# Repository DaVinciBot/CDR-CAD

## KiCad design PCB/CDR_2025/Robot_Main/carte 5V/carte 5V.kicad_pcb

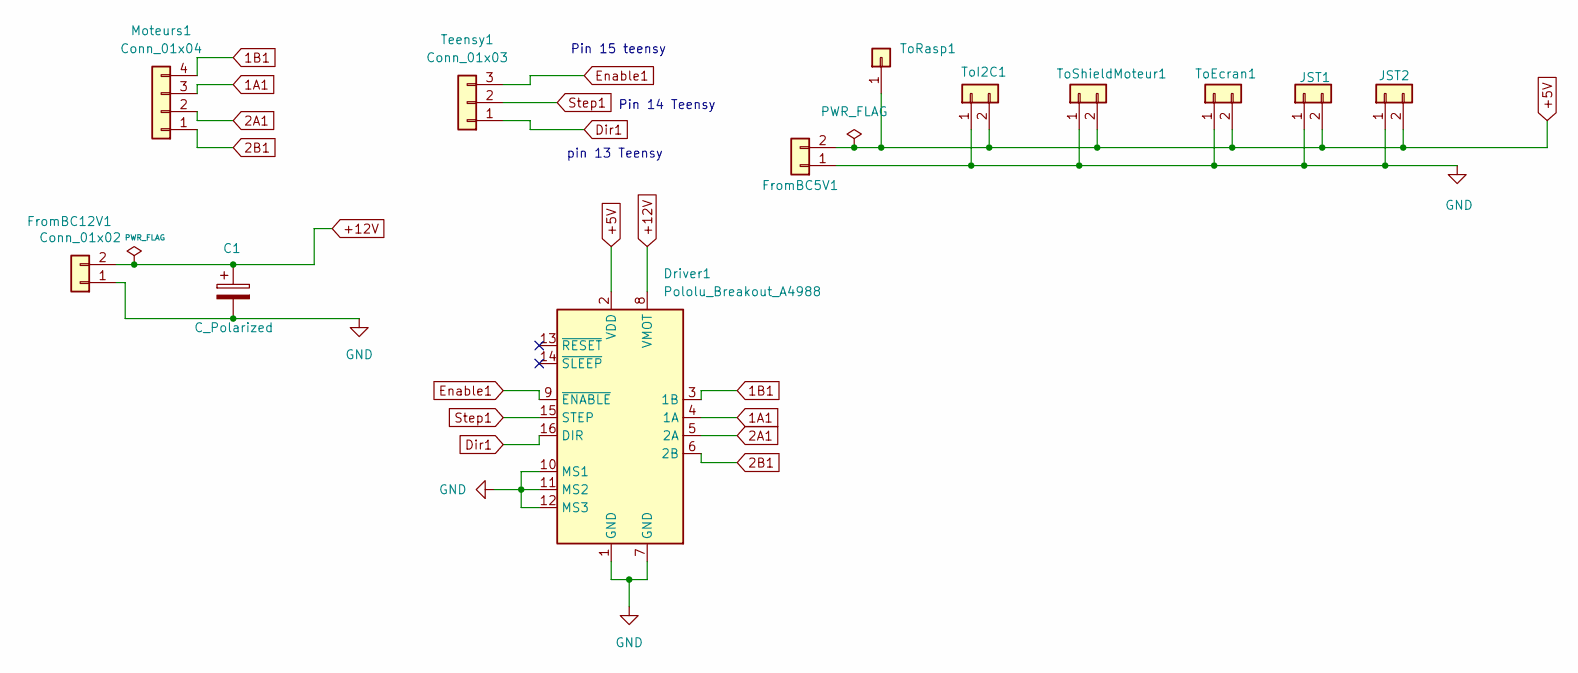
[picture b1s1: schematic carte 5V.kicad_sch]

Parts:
C1: C_Polarized; C_Radial_D12.5mm_H25.0mm_P5.00mm
Driver1: Pololu_Breakout_A4988; Pololu_Breakout-16_15.2x20.3mm
FromBC5V1, FromBC12V1: Conn_01x02; TerminalBlock_bornier-2_P5.08mm
JST1, JST2: Conn_01x02; JST_XH_B2B-XH-A_1x02_P2.50mm_Vertical
Moteurs1: Conn_01x04; JST_XH_B4B-XH-A_1x04_P2.50mm_Vertical
Teensy1: Conn_01x03; JST_XH_B3B-XH-A_1x03_P2.50mm_Vertical
ToEcran1: Conn_01x02; JST_XH_B2B-XH-A_1x02_P2.50mm_Vertical
ToI2C1: Conn_01x02; JST_XH_B2B-XH-A_1x02_P2.50mm_Vertical
ToRasp1: Conn_01x01; JST_XH_B1B-XH-AM_1x01_P2.50mm_Vertical
ToShieldMoteur1: Conn_01x02; JST_XH_B2B-XH-A_1x02_P2.50mm_Vertical

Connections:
1A1: Driver1.4 (1A), Moteurs1.3
1B1: Driver1.3 (1B), Moteurs1.4
2A1: Driver1.5 (2A), Moteurs1.2
2B1: Driver1.6 (2B), Moteurs1.1
+5V: Driver1.2 (VDD), FromBC5V1.2, JST1.2, JST2.2, ToEcran1.2, ToI2C1.2, ToRasp1.1, ToShieldMoteur1.2
+12V: C1.1, Driver1.8 (VMOT), FromBC12V1.2
Dir1: Driver1.16 (DIR), Teensy1.1
Enable1: Driver1.9 (~ENABLE), Teensy1.3
GND: C1.2, Driver1.1 (GND), Driver1.7 (GND), Driver1.10 (MS1), Driver1.11 (MS2), Driver1.12 (MS3), FromBC5V1.1, FromBC12V1.1, JST1.1, JST2.1, ToEcran1.1, ToI2C1.1, ToShieldMoteur1.1
Step1: Driver1.15 (STEP), Teensy1.2

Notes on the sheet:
Pin 15 teensy
Pin 14 Teensy
pin 13 Teensy

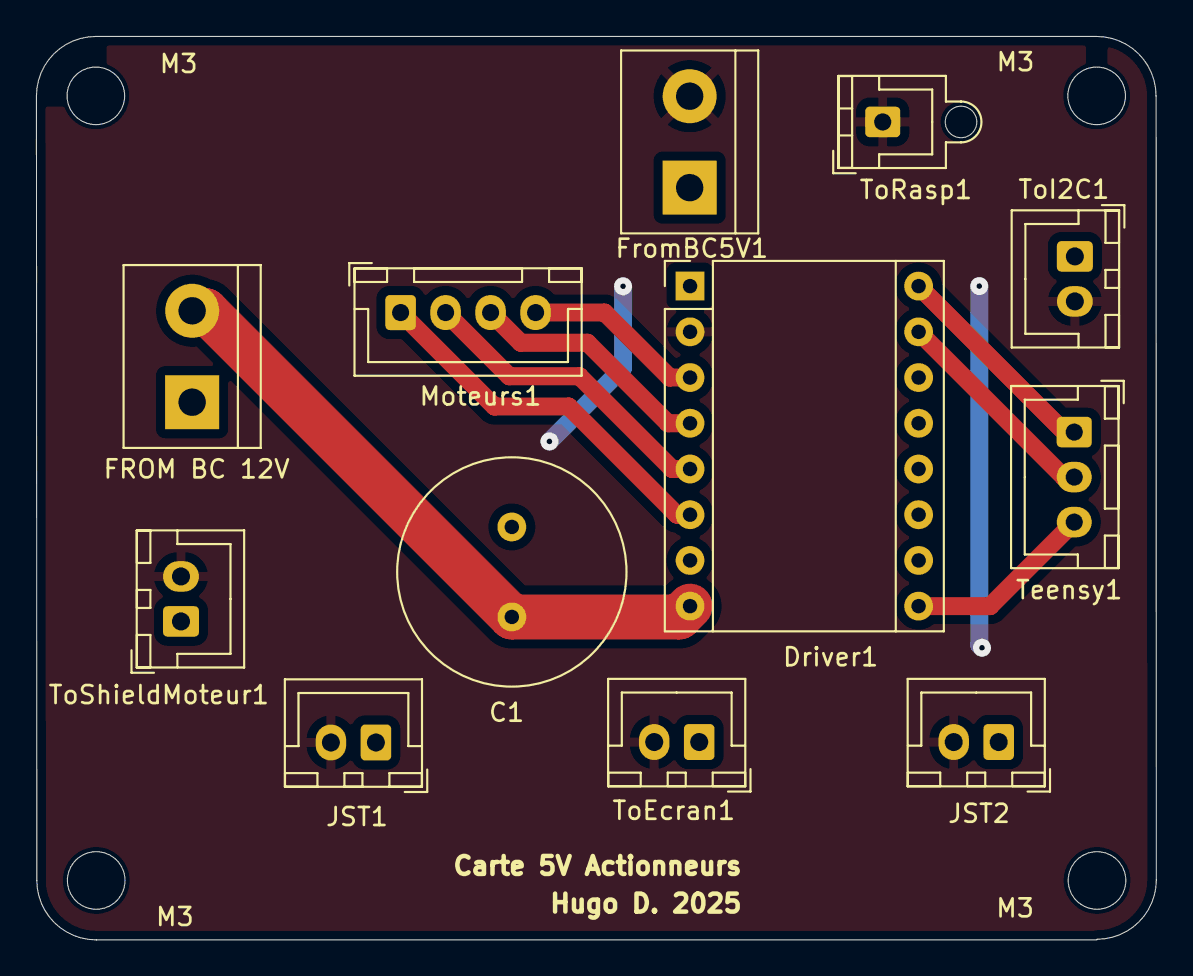
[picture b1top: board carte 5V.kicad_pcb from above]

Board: 2 copper layers, 62.2 x 50.2 mm, 16 parts (0 on the bottom side), 10 nets.

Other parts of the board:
M3, M3#2, M3#3, M3#4: MountingHole_3.2mm_M3

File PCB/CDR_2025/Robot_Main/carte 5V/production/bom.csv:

Designator,Footprint,Quantity,Value,LCSC Part #
C1,C_Radial_D12.5mm_H25.0mm_P5.00mm,1,C_Polarized,
DRIVER1,Pololu_Breakout-16_15.2x20.3mm,1,Pololu_Breakout_A4988,
"FROMBC12V1, FROMBC5V1",TerminalBlock_bornier-2_P5.08mm,2,Conn_01x02,
"JST1, JST2, TOECRAN1, TOI2C1, TOSHIELDMOTEUR1",JST_XH_B2B-XH-A_1x02_P2.50mm_Vertical,5,Conn_01x02,
MOTEURS1,JST_XH_B4B-XH-A_1x04_P2.50mm_Vertical,1,Conn_01x04,
TEENSY1,JST_XH_B3B-XH-A_1x03_P2.50mm_Vertical,1,Conn_01x03,
TORASP1,JST_XH_B1B-XH-AM_1x01_P2.50mm_Vertical,1,Conn_01x01,

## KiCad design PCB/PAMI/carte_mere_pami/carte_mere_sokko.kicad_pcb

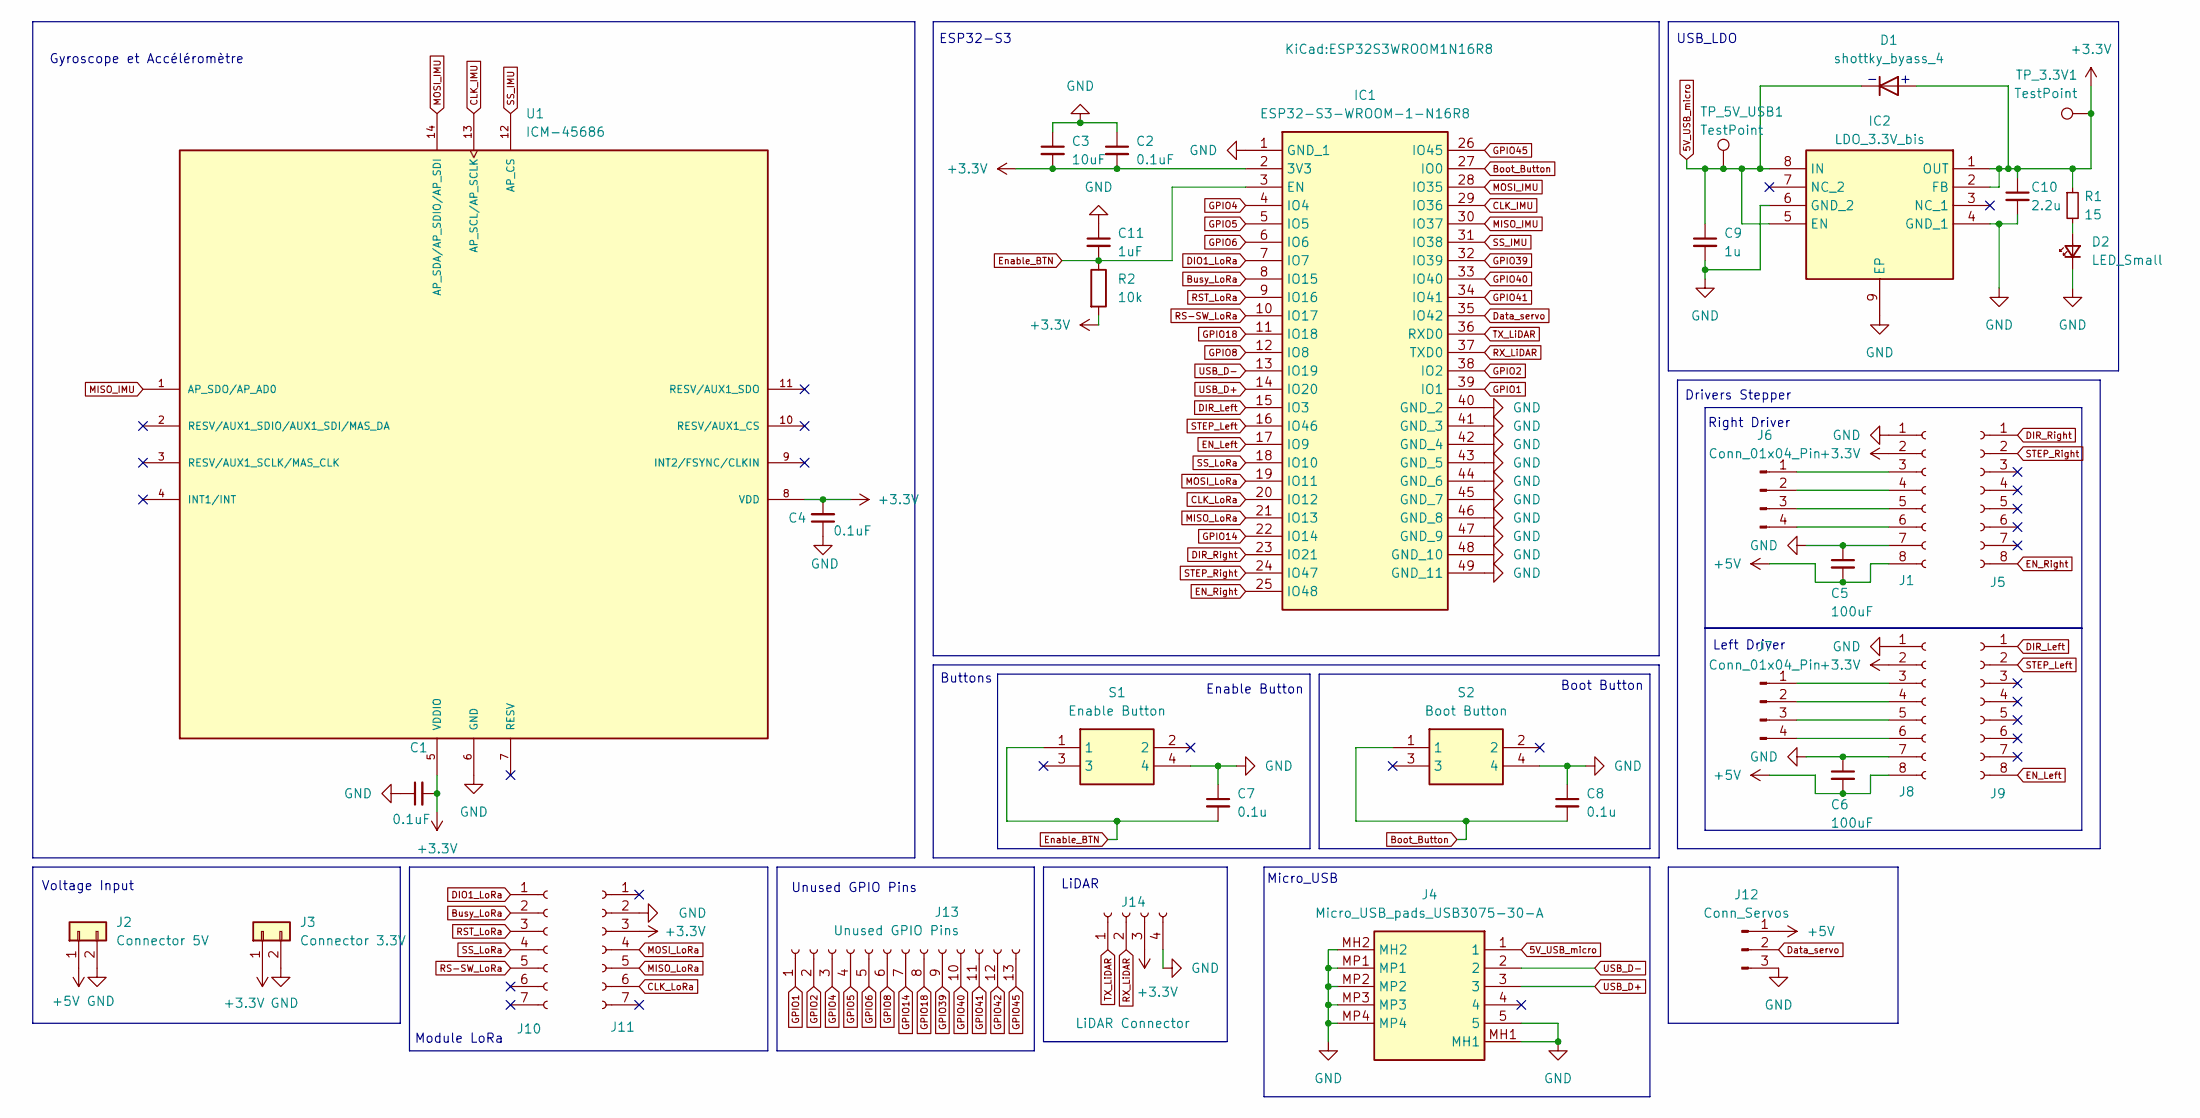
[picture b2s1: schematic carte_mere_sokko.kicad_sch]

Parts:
C1, C2, C4: 0.1uF; C_0805_2012Metric_Pad1.18x1.45mm_HandSolder
C3: 10uF; C_0805_2012Metric_Pad1.18x1.45mm_HandSolder
C5, C6: 100uF; C_0805_2012Metric_Pad1.18x1.45mm_HandSolder
C7, C8: 0.1u; C_0805_2012Metric_Pad1.18x1.45mm_HandSolder
C9: 1u; C_0402_1005Metric_Pad0.74x0.62mm_HandSolder
C10: 2.2u; C_0805_2012Metric_Pad1.18x1.45mm_HandSolder
C11: 1uF; C_0805_2012Metric_Pad1.18x1.45mm_HandSolder
D1: shottky_byass_4; SOD2512X113N
D2: LED_Small; LED_0603_1608Metric_Pad1.05x0.95mm_HandSolder
IC1: ESP32-S3-WROOM-1-N16R8; ESP32S3WROOM1N16R8; Manufacturer_Part_Number ESP32-S3-WROOM-1-N16R8; Mouser Part Number 356-ESP32S3WRM1N16R8
IC2: LDO_3.3V_bis; SOP65P490X110-9N; Manufacturer_Part_Number TLV76701DGNR; Mouser Part Number 595-TLV76701DGNR
J1, J5, J8, J9: Conn_01x08_Socket; PinSocket_1x08_P2.54mm_Vertical
J2: Connector 5V; JST_XH_B2B-XH-A_1x02_P2.50mm_Vertical
J3: Connector 3.3V; JST_XH_B2B-XH-A_1x02_P2.50mm_Vertical
J4: Micro_USB_pads_USB3075-30-A; USB307530A; Manufacturer_Part_Number USB3075-30-A; Mouser Part Number 640-USB3075-30-A
J6, J7: Conn_01x04_Pin; JST_XH_B4B-XH-A_1x04_P2.50mm_Vertical
J10, J11: Conn_01x07_Socket; PinHeader_1x07_P2.54mm_Vertical
J12: Conn_Servos; PinHeader_1x03_P2.00mm_Vertical
J13: Unused GPIO Pins; PinSocket_1x13_P2.54mm_Vertical
J14: LiDAR Connector; PinSocket_1x04_P2.54mm_Vertical
R1: 15; R_0805_2012Metric_Pad1.20x1.40mm_HandSolder
R2: 10k; R_0805_2012Metric_Pad1.20x1.40mm_HandSolder
S1: Enable Button; PTS810SJG250SMTRLFS; Manufacturer_Part_Number PTS810SJM250SMTRLFS; Mouser Part Number 611-PTS810SJM250SMTR
S2: Boot Button; PTS810SJG250SMTRLFS; Manufacturer_Part_Number PTS810SJM250SMTRLFS; Mouser Part Number 611-PTS810SJM250SMTR
TP_3.3V1, TP_5V_USB1: TestPoint; TestPoint_Pad_D2.0mm
U1: ICM-45686; IC_ICM-45686; PARTREV 0.2

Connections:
5V_USB_micro: C9.1, D1.1 (K), IC2.5 (EN), IC2.8 (IN), J4.1, TP_5V_USB1.1
+3.3V: C1.2, C2.2, C3.2, C4.2, C10.1, D1.2 (A), IC1.2 (3V3), IC2.1 (OUT), IC2.2 (FB), J1.2, J3.1, J8.2, J11.3, J14.3, R1.1, R2.2, TP_3.3V1.1, U1.5 (VDDIO), U1.8 (VDD)
+5V: C5.2, C6.2, J1.8, J2.1, J8.8, J12.1
Boot_Button: C8.2, IC1.27 (IO0), S2.1
Busy_LoRa: IC1.8 (IO15), J10.2
CLK_IMU: IC1.29 (IO36), U1.13 (AP_SCL/AP_SCLK)
CLK_LoRa: IC1.20 (IO12), J11.6
DIO1_LoRa: IC1.7 (IO7), J10.1
DIR_Left: IC1.15 (IO3), J9.1
DIR_Right: IC1.23 (IO21), J5.1
Data_servo: IC1.35 (IO42), J12.2
EN_Left: IC1.17 (IO9), J9.8
EN_Right: IC1.25 (IO48), J5.8
Enable_BTN: C7.2, C11.2, IC1.3 (EN), R2.1, S1.1
GND: C1.1, C2.1, C3.1, C4.1, C5.1, C6.1, C7.1, C8.1, C9.2, C10.2, C11.1, D2.1 (K), IC1.1 (GND_1), IC1.40 (GND_2), IC1.41 (GND_3), IC1.42 (GND_4), IC1.43 (GND_5), IC1.44 (GND_6), IC1.45 (GND_7), IC1.46 (GND_8), IC1.47 (GND_9), IC1.48 (GND_10), IC1.49 (GND_11), IC2.4 (GND_1), IC2.6 (GND_2), IC2.9 (EP), J1.1, J1.7, J2.2, J3.2, J4.5, J4.MH1, J4.MH2, J4.MP1, J4.MP2, J4.MP3, J4.MP4, J8.1, J8.7, J11.2, J12.3, J14.4, S1.4, S2.4, U1.6 (GND)
GPIO1: IC1.39 (IO1), J13.1
GPIO2: IC1.38 (IO2), J13.2
GPIO4: IC1.4 (IO4), J13.3
GPIO5: IC1.5 (IO5), J13.4
GPIO6: IC1.6 (IO6), J13.5
GPIO8: IC1.12 (IO8), J13.6
GPIO14: IC1.22 (IO14), J13.7
GPIO18: IC1.11 (IO18), J13.8
GPIO39: IC1.32 (IO39), J13.9
GPIO40: IC1.33 (IO40), J13.10
GPIO41: IC1.34 (IO41), J13.11
GPIO45: IC1.26 (IO45), J13.13
MISO_IMU: IC1.30 (IO37), U1.1 (AP_SDO/AP_AD0)
MISO_LoRa: IC1.21 (IO13), J11.5
MOSI_IMU: IC1.28 (IO35), U1.14 (AP_SDA/AP_SDIO/AP_SDI)
MOSI_LoRa: IC1.19 (IO11), J11.4
unnamed: D2.2 (A), R1.2
unnamed: J1.3, J6.1
unnamed: J1.4, J6.2
unnamed: J1.5, J6.3
unnamed: J1.6, J6.4
unnamed: J7.1, J8.3
unnamed: J7.2, J8.4
unnamed: J7.3, J8.5
unnamed: J7.4, J8.6
RS-SW_LoRa: IC1.10 (IO17), J10.5
RST_LoRa: IC1.9 (IO16), J10.3
RX_LiDAR: IC1.37 (TXD0), J14.2
SS_IMU: IC1.31 (IO38), U1.12 (AP_CS)
SS_LoRa: IC1.18 (IO10), J10.4
STEP_Left: IC1.16 (IO46), J9.2
STEP_Right: IC1.24 (IO47), J5.2
TX_LiDAR: IC1.36 (RXD0), J14.1
USB_D+: IC1.14 (IO20), J4.3
USB_D-: IC1.13 (IO19), J4.2

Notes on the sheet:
Voltage Input
Right Driver
ESP32-S3
LiDAR
Drivers Stepper
Buttons
USB_LDO
Enable Button
Unused GPIO Pins
Gyroscope et Accéléromètre
Left Driver
Boot Button
Module LoRa
Micro_USB

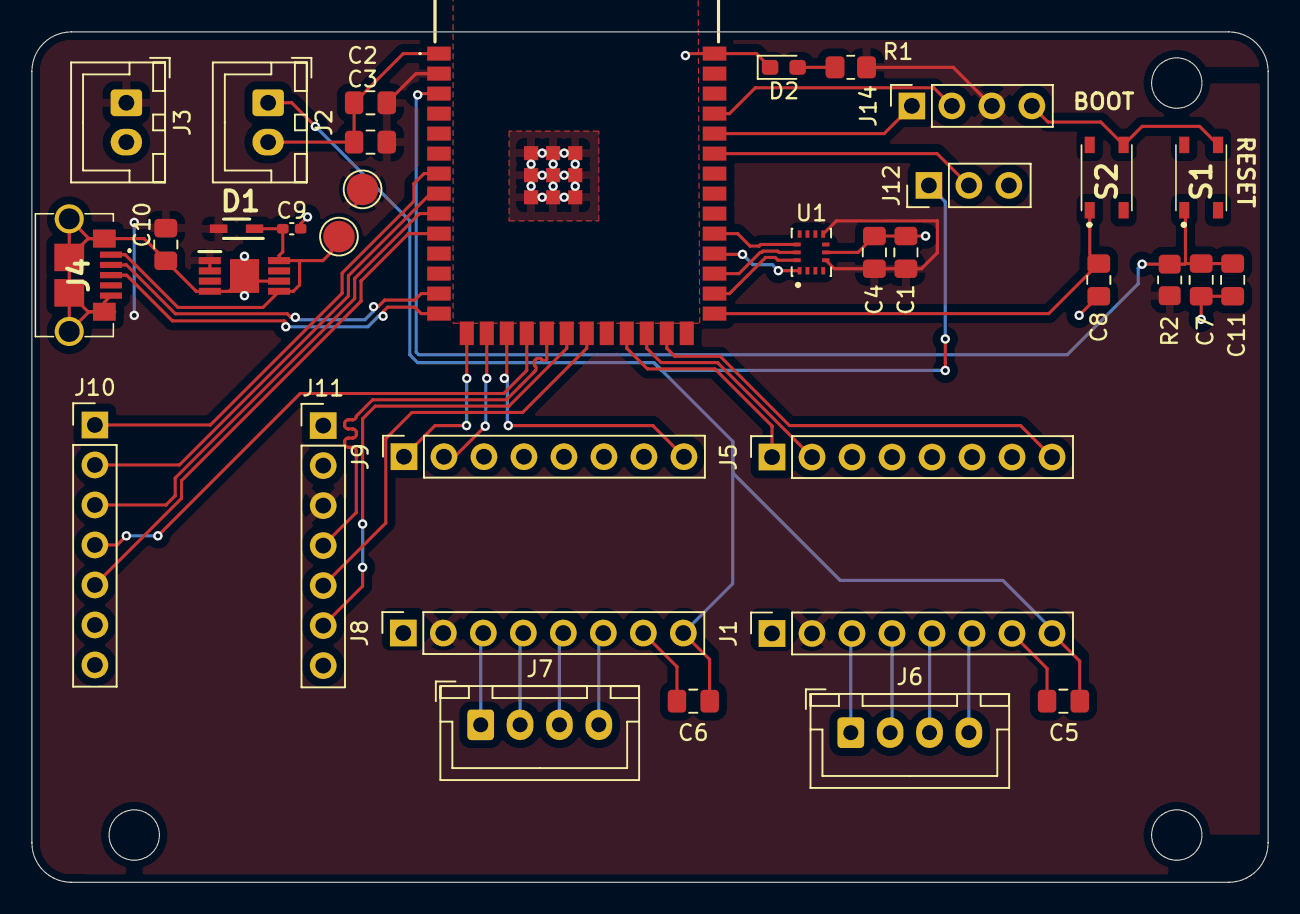
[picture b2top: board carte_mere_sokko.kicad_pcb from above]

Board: 2 copper layers, 78.5 x 54.0 mm, 35 parts (0 on the bottom side), 38 nets.

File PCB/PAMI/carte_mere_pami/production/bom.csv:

Designator,Footprint,Quantity,Value,LCSC Part #
"C1, C2, C4",0805,3,0.1uF,
C10,0805,1,2.2u,
C11,0805,1,1uF,
C3,0805,1,10uF,
"C5, C6",0805,2,100uF,
"C7, C8",0805,2,0.1u,
C9,0402,1,1u,
D1,SOD2512X113N,1,shottky_byass_4,
D2,0603,1,LED_Small,
IC1,ESP32S3WROOM1N16R8,1,ESP32-S3-WROOM-1-N16R8,
IC2,SOP65P490X110-9N,1,LDO_3.3V_bis,
"J1, J5, J8, J9",PinSocket_1x08_P2.54mm_Vertical,4,Conn_01x08_Socket,
"J10, J11",PinHeader_1x07_P2.54mm_Vertical,2,Conn_01x07_Socket,
J12,PinHeader_1x03_P2.00mm_Vertical,1,Conn_Servos,
J14,PinSocket_1x04_P2.54mm_Vertical,1,LiDAR Connector,
J2,JST_XH_B2B-XH-A_1x02_P2.50mm_Vertical,1,Connector 5V,
J3,JST_XH_B2B-XH-A_1x02_P2.50mm_Vertical,1,Connector 3.3V,
J4,USB307530A,1,Micro_USB_pads_USB3075-30-A,
"J6, J7",JST_XH_B4B-XH-A_1x04_P2.50mm_Vertical,2,Conn_01x04_Pin,
R1,0805,1,15,
R2,0805,1,10k,
S1,PTS810SJG250SMTRLFS,1,Enable Button,
S2,PTS810SJG250SMTRLFS,1,Boot Button,
"TP_3.3V1, TP_5V_USB1",TestPoint_Pad_D2.0mm,2,TestPoint,
U1,IC_ICM-45686,1,ICM-45686,

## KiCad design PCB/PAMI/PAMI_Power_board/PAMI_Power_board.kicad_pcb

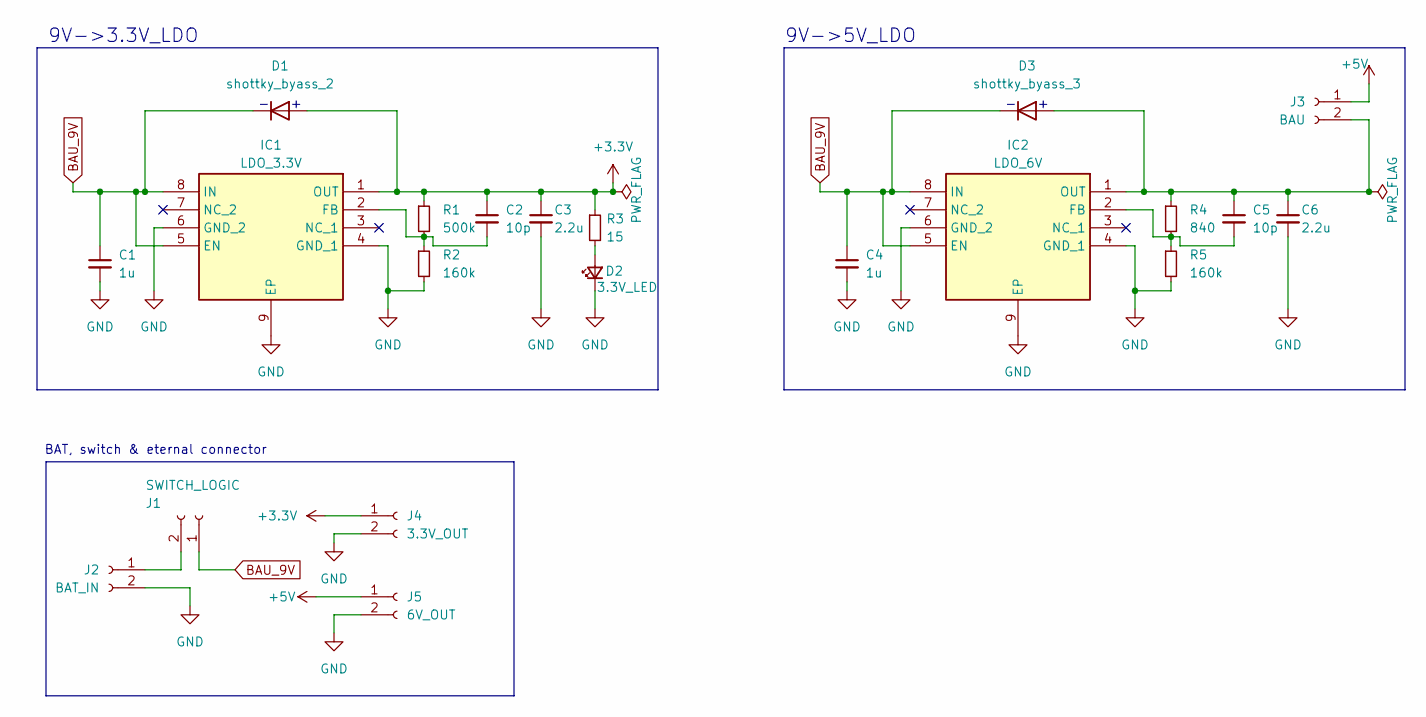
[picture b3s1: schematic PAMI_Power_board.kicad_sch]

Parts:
C1, C4: 1u; C_0402_1005Metric_Pad0.74x0.62mm_HandSolder
C2, C5: 10p; C_0805_2012Metric_Pad1.18x1.45mm_HandSolder
C3, C6: 2.2u; C_0805_2012Metric_Pad1.18x1.45mm_HandSolder
D1: shottky_byass_2; SOD2512X113N
D2: 3.3V_LED; ASCKCG00NW5X5020302
D3: shottky_byass_3; SOD2512X113N
IC1: LDO_3.3V; SOP65P490X110-9N; Manufacturer_Part_Number TLV76701DGNR; Mouser Part Number 595-TLV76701DGNR
IC2: LDO_6V; SOP65P490X110-9N; Manufacturer_Part_Number TLV76701DGNR; Mouser Part Number 595-TLV76701DGNR
J1: SWITCH_LOGIC; JST_XH_B2B-XH-A_1x02_P2.50mm_Vertical
J2: BAT_IN; JST_XH_B2B-XH-A_1x02_P2.50mm_Vertical
J3: BAU; JST_XH_B2B-XH-A_1x02_P2.50mm_Vertical
J4: 3.3V_OUT; JST_XH_B2B-XH-A_1x02_P2.50mm_Vertical
J5: 6V_OUT; JST_XH_B2B-XH-A_1x02_P2.50mm_Vertical
R1: 500k; R_0805_2012Metric_Pad1.20x1.40mm_HandSolder
R2, R5: 160k; R_0805_2012Metric_Pad1.20x1.40mm_HandSolder
R3: 15; R_0805_2012Metric_Pad1.20x1.40mm_HandSolder
R4: 840; R_0805_2012Metric_Pad1.20x1.40mm_HandSolder

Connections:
+3.3V: C2.1, C3.1, D1.2 (A), IC1.1 (OUT), J4.1, R1.1, R3.1
+5V: J3.1, J5.1
BAU_9V: C1.1, C4.1, D1.1 (K), D3.1 (K), IC1.5 (EN), IC1.8 (IN), IC2.5 (EN), IC2.8 (IN), J1.1
GND: C1.2, C3.2, C4.2, C6.2, D2.1 (K), IC1.4 (GND_1), IC1.6 (GND_2), IC1.9 (EP), IC2.4 (GND_1), IC2.6 (GND_2), IC2.9 (EP), J2.2, J4.2, J5.2, R2.2, R5.2; also elsewhere on the board
unnamed: D2.2 (A), R3.2
unnamed 5: C5.1, C6.1, D3.2 (A), IC2.1 (OUT), J3.2, R4.1; also elsewhere on the board
unnamed: C2.2, IC1.2 (FB), R1.2, R2.1
unnamed: C5.2, IC2.2 (FB), R4.2, R5.1
Switch: J1.2, J2.1

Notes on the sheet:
9V->3.3V_LDO
9V->5V_LDO
BAT, switch & eternal connector

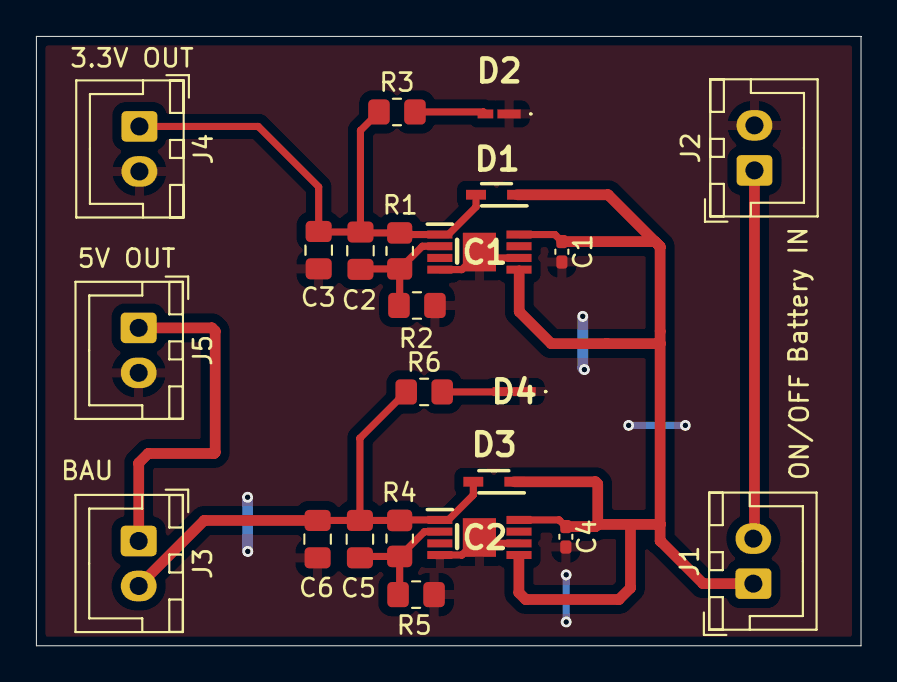
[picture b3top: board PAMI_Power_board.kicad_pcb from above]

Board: 2 copper layers, 45.8 x 33.8 mm, 23 parts (0 on the bottom side), 10 nets.

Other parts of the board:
D4: 6V_LED; ASCKCG00NW5X5020302
R6: 135; R_0805_2012Metric_Pad1.20x1.40mm_HandSolder

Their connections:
GND: D4.1 (K); also elsewhere on the board
unnamed 5: R6.1; also elsewhere on the board
unnamed: D4.2 (A), R6.2

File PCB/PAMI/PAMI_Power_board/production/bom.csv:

Designator,Footprint,Quantity,Value,LCSC Part #
"C1, C4",0402,2,1u,
"C2, C5",0805,2,10p,
"C3, C6",0805,2,2.2u,
D1,SOD2512X113N,1,shottky_byass_2,
D2,ASCKCG00NW5X5020302,1,3.3V_LED,
D3,SOD2512X113N,1,shottky_byass_3,
D4,ASCKCG00NW5X5020302,1,6V_LED,
IC1,SOP65P490X110-9N,1,LDO_3.3V,
IC2,SOP65P490X110-9N,1,LDO_6V,
J1,JST_XH_B2B-XH-A_1x02_P2.50mm_Vertical,1,SWITCH_LOGIC,
J2,JST_XH_B2B-XH-A_1x02_P2.50mm_Vertical,1,BAT_IN,
J3,JST_XH_B2B-XH-A_1x02_P2.50mm_Vertical,1,BAU,
J4,JST_XH_B2B-XH-A_1x02_P2.50mm_Vertical,1,3.3V_OUT,
J5,JST_XH_B2B-XH-A_1x02_P2.50mm_Vertical,1,5V_OUT,
R1,0805,1,500k,
"R2, R5",0805,2,160k,
R3,0805,1,15,
R4,0805,1,840,
R6,0805,1,135,

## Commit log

2024-01-23 TAYOOOOO le repo
2024-01-29 Transfert de Grab-CAD vers Github
2024-02-03 Ajout de la modé du bras articulé
    (merci Théo)
2024-02-13 sauvgarde actionneurs pince multiple
2024-02-15 Réorganisation servo + main de dieu
2024-02-19 sauvegarde hebdo
2024-03-05 Panneau Solaire et Zone de calcul
    Création de l'actionneur de panneau solaire ainsi que de la structure de la zone de calcul
2024-03-12 Sauvegarde Hebdomadaire
2024-03-19 Nouvelle version des éléments de jeu .step .stl / + autres
    Autres :
    Etage elec
    Support de camera Razer
2024-03-21 Ajout du toit_proto
2024-04-08 Modification lidar
2024-04-30 Sauvegarde pré-rush
2024-05-04 Joute Solaire
2024-05-05 roues encodeuses de rechanges
2024-10-26 MAJ version finale 2024
2025-01-13 robot proto 2025
2025-02-25 support_moteurs
2025-04-10 grosse sauvegarde
2025-04-23 Add PAMI
2025-04-23 PAMI v2
2025-05-11 Add PAMI PCB and PAMI v3, and remove SW temp file
2025-05-11 Routing nearly done
2025-05-12 Smaller
2025-05-12 PCB PAMI Nearly done, lack ground plane
2025-05-13 V2 PAMI Motherboard
2025-05-21 pre ccompetition
2025-05-21 pre competition 2
2025-05-21 pre competition 3
2025-05-28 Fix PCB
2025-05-28 PAMI v4 from Damien's drive
2025-05-29 Improve PAMI motherboard
    Change footprint for the servo header
    link the 3.3 plane to improve reliability
2025-06-05 Update hole position
2025-06-14 Post CDR fix
2025-09-29 2025 save last version
2026-01-05 biboup
